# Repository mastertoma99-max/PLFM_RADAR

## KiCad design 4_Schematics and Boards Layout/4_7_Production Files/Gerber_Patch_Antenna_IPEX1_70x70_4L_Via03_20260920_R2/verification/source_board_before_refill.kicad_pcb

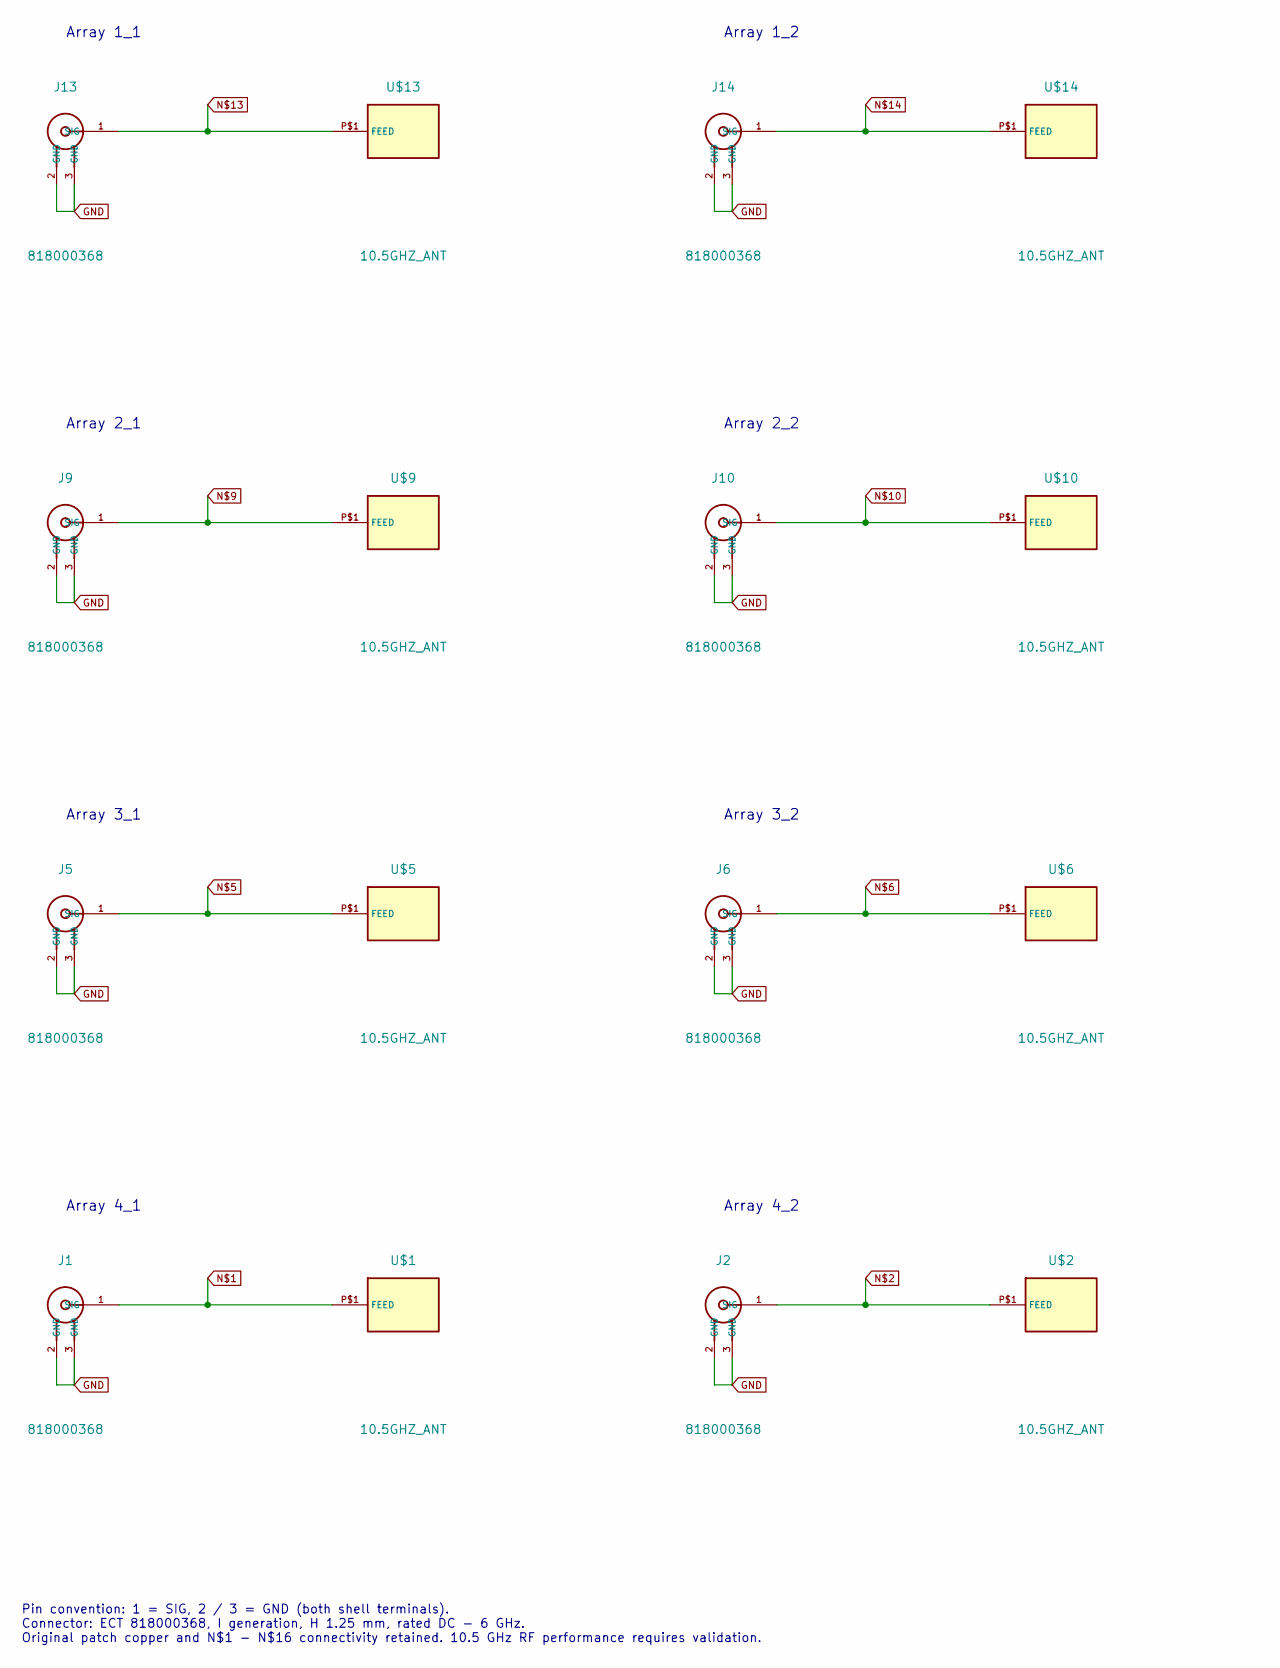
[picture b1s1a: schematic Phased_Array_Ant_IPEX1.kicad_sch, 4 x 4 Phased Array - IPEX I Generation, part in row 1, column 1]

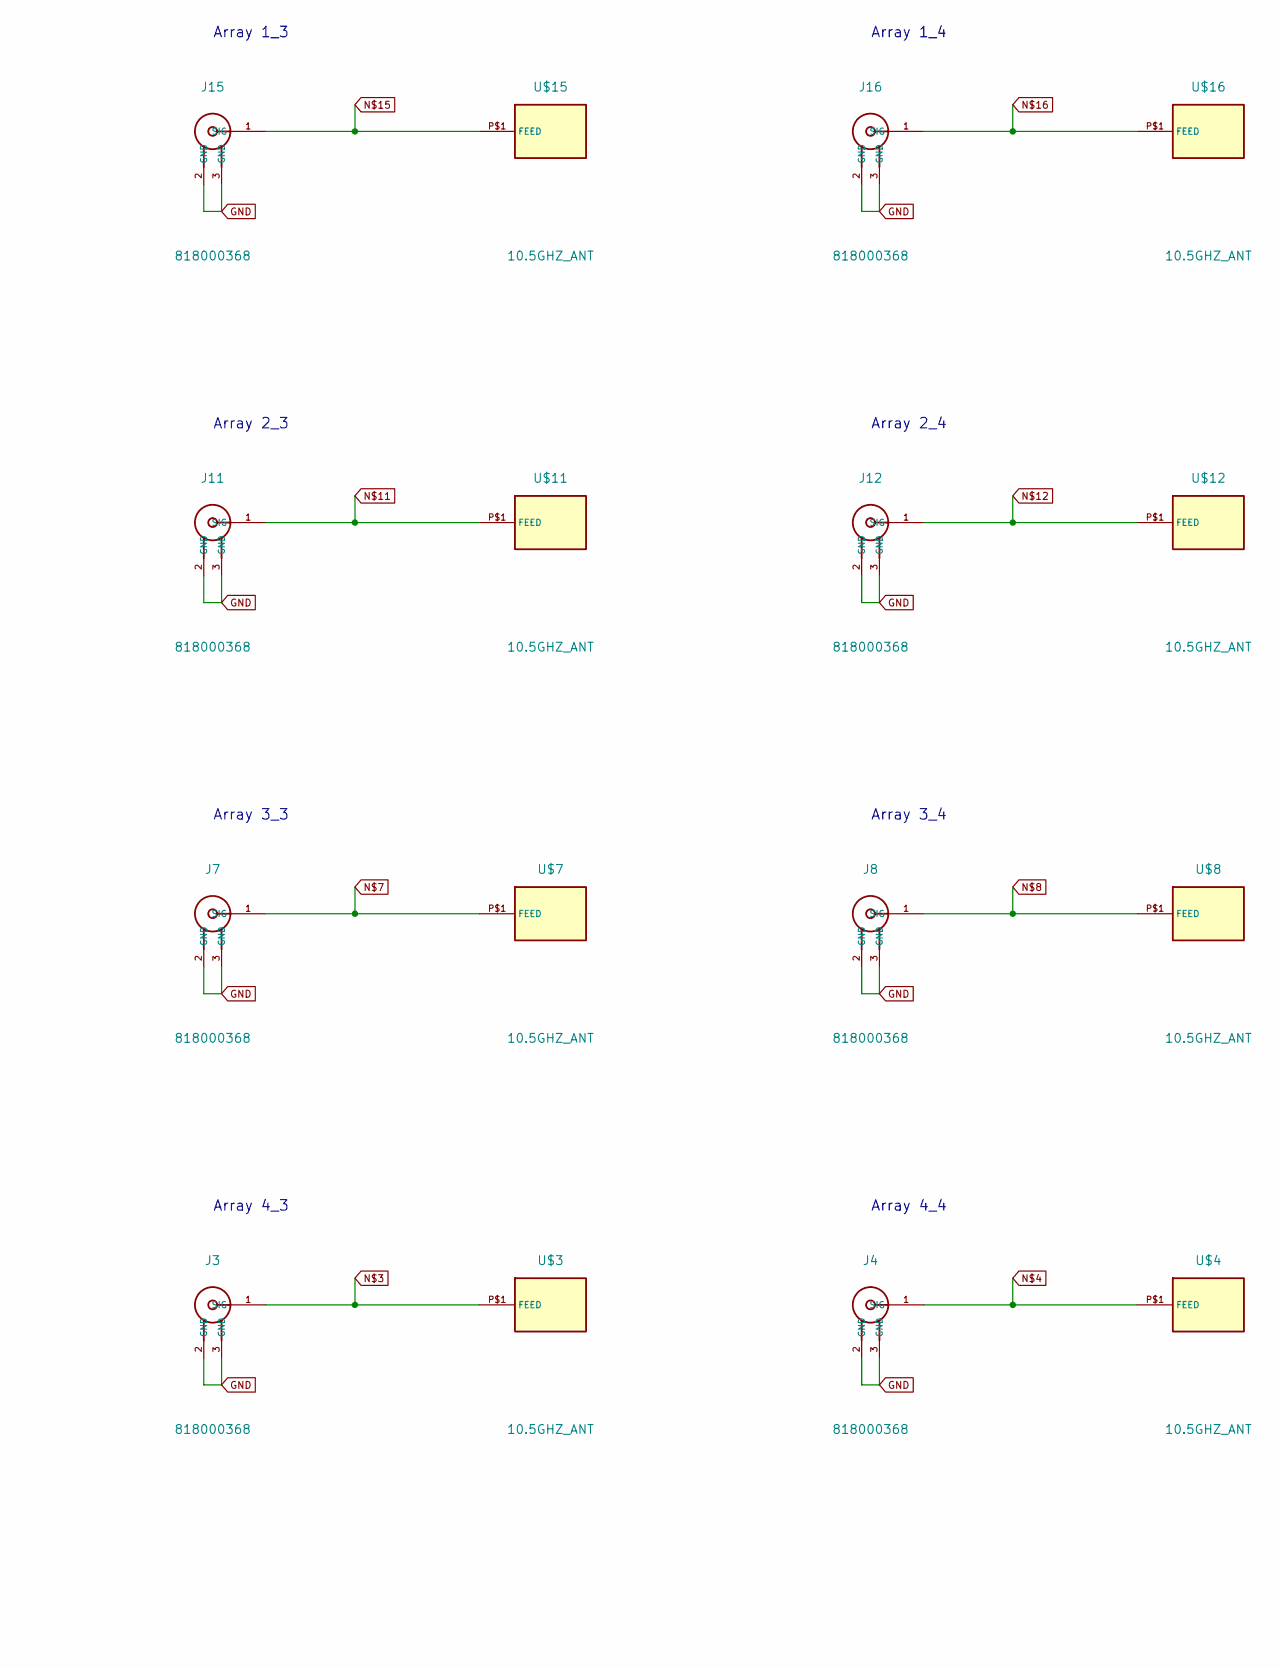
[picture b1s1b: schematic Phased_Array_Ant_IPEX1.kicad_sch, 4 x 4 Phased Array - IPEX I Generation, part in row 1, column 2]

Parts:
J1, J2, J3, J4, J5, J6, J7, J8, J9, J10, J11, J12, J13, J14, J15, J16: 818000368; ECT_818000368_IPEX1_1.25mm; MPN 818000368
U$1, U$2, U$3, U$4, U$5, U$6, U$7, U$8, U$9, U$10, U$11, U$12, U$13, U$14, U$15, U$16: 10.5GHZ_ANT; Patch_10p5GHz_9.538x7.636mm

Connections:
GND: J1.2 (GND), J1.3 (GND), J2.2 (GND), J2.3 (GND), J3.2 (GND), J3.3 (GND), J4.2 (GND), J4.3 (GND), J5.2 (GND), J5.3 (GND), J6.2 (GND), J6.3 (GND), J7.2 (GND), J7.3 (GND), J8.2 (GND), J8.3 (GND), J9.2 (GND), J9.3 (GND), J10.2 (GND), J10.3 (GND), J11.2 (GND), J11.3 (GND), J12.2 (GND), J12.3 (GND), J13.2 (GND), J13.3 (GND), J14.2 (GND), J14.3 (GND), J15.2 (GND), J15.3 (GND), J16.2 (GND), J16.3 (GND)
unnamed: J1.1 (SIG), U$1.P$1
unnamed: J2.1 (SIG), U$2.P$1
unnamed: J3.1 (SIG), U$3.P$1
unnamed: J4.1 (SIG), U$4.P$1
unnamed: J5.1 (SIG), U$5.P$1
unnamed: J6.1 (SIG), U$6.P$1
unnamed: J7.1 (SIG), U$7.P$1
unnamed: J8.1 (SIG), U$8.P$1
unnamed: J9.1 (SIG), U$9.P$1
unnamed: J10.1 (SIG), U$10.P$1
unnamed: J11.1 (SIG), U$11.P$1
unnamed: J12.1 (SIG), U$12.P$1
unnamed: J13.1 (SIG), U$13.P$1
unnamed: J14.1 (SIG), U$14.P$1
unnamed: J15.1 (SIG), U$15.P$1
unnamed: J16.1 (SIG), U$16.P$1

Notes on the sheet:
Array 3_4
Array 3_1
Array 1_4
Array 4_1
Array 4_4
Array 3_3
Array 1_1
Array 1_3
Array 2_3
Array 2_1
Array 4_3
Array 1_2
Array 2_2
Array 3_2
Array 2_4
Array 4_2
Pin convention: 1 = SIG, 2 / 3 = GND (both shell terminals). Connector: ECT 818000368, I generation, H 1.25 mm, rated DC - 6 GHz. Original patch copper and N$1 - N$16 connectivity retained. 10.5 GHz RF performance requires validation.

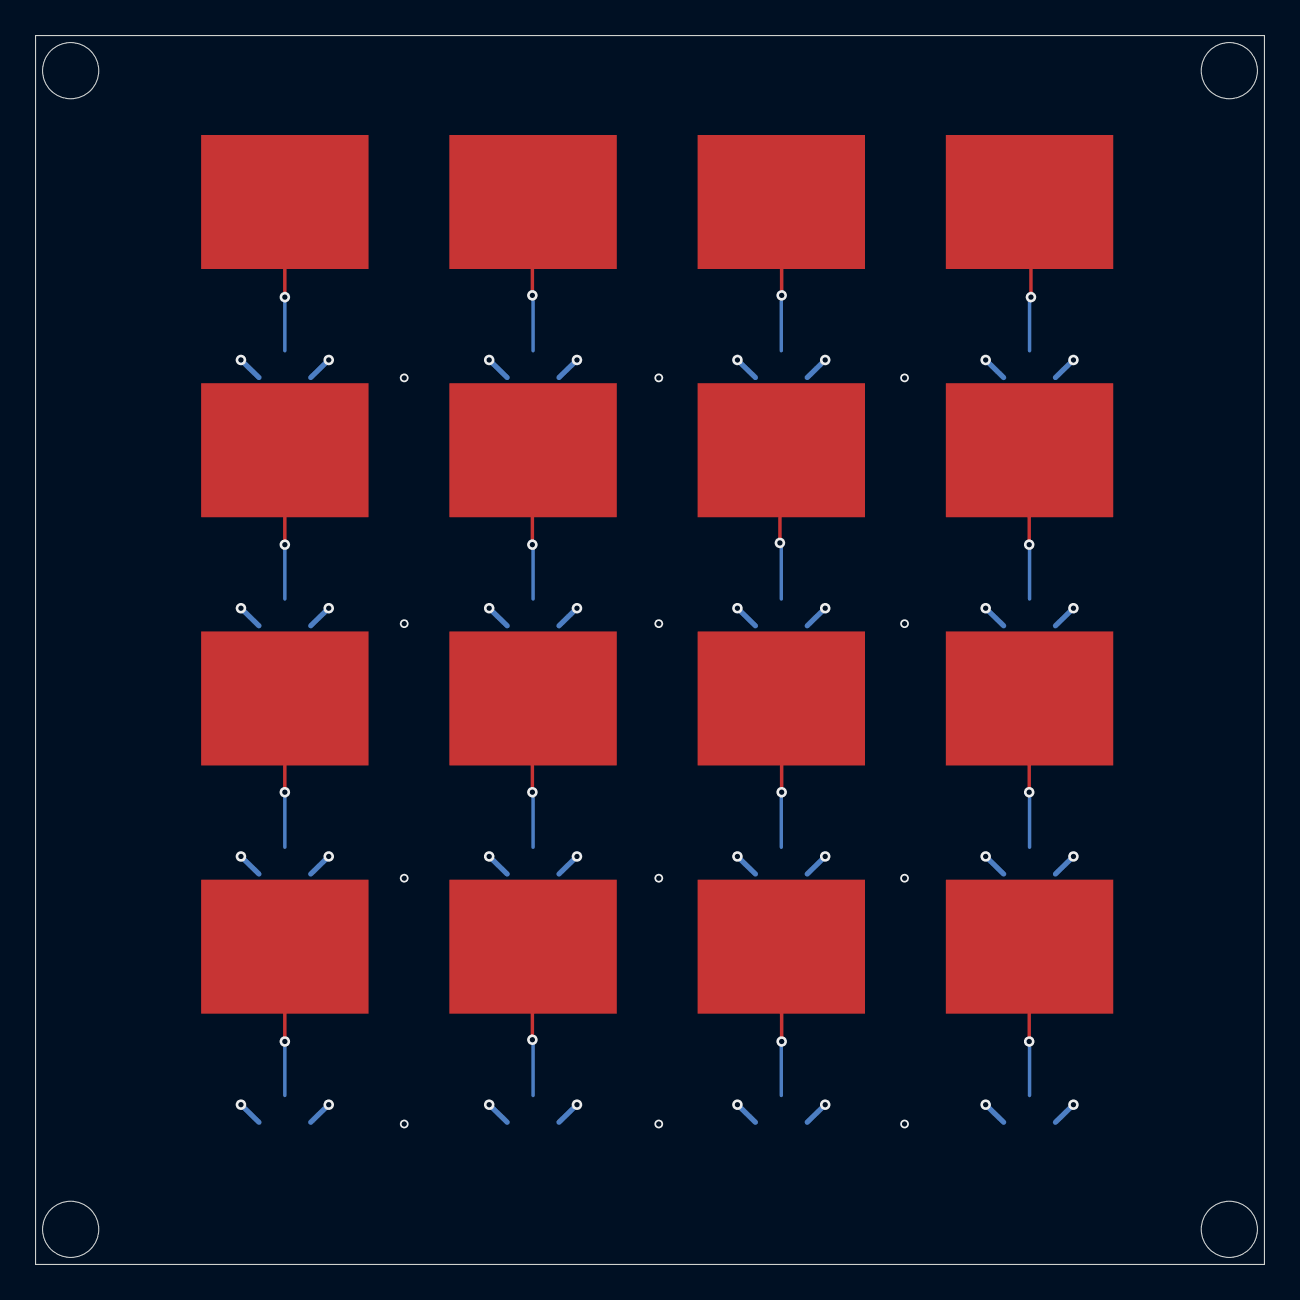
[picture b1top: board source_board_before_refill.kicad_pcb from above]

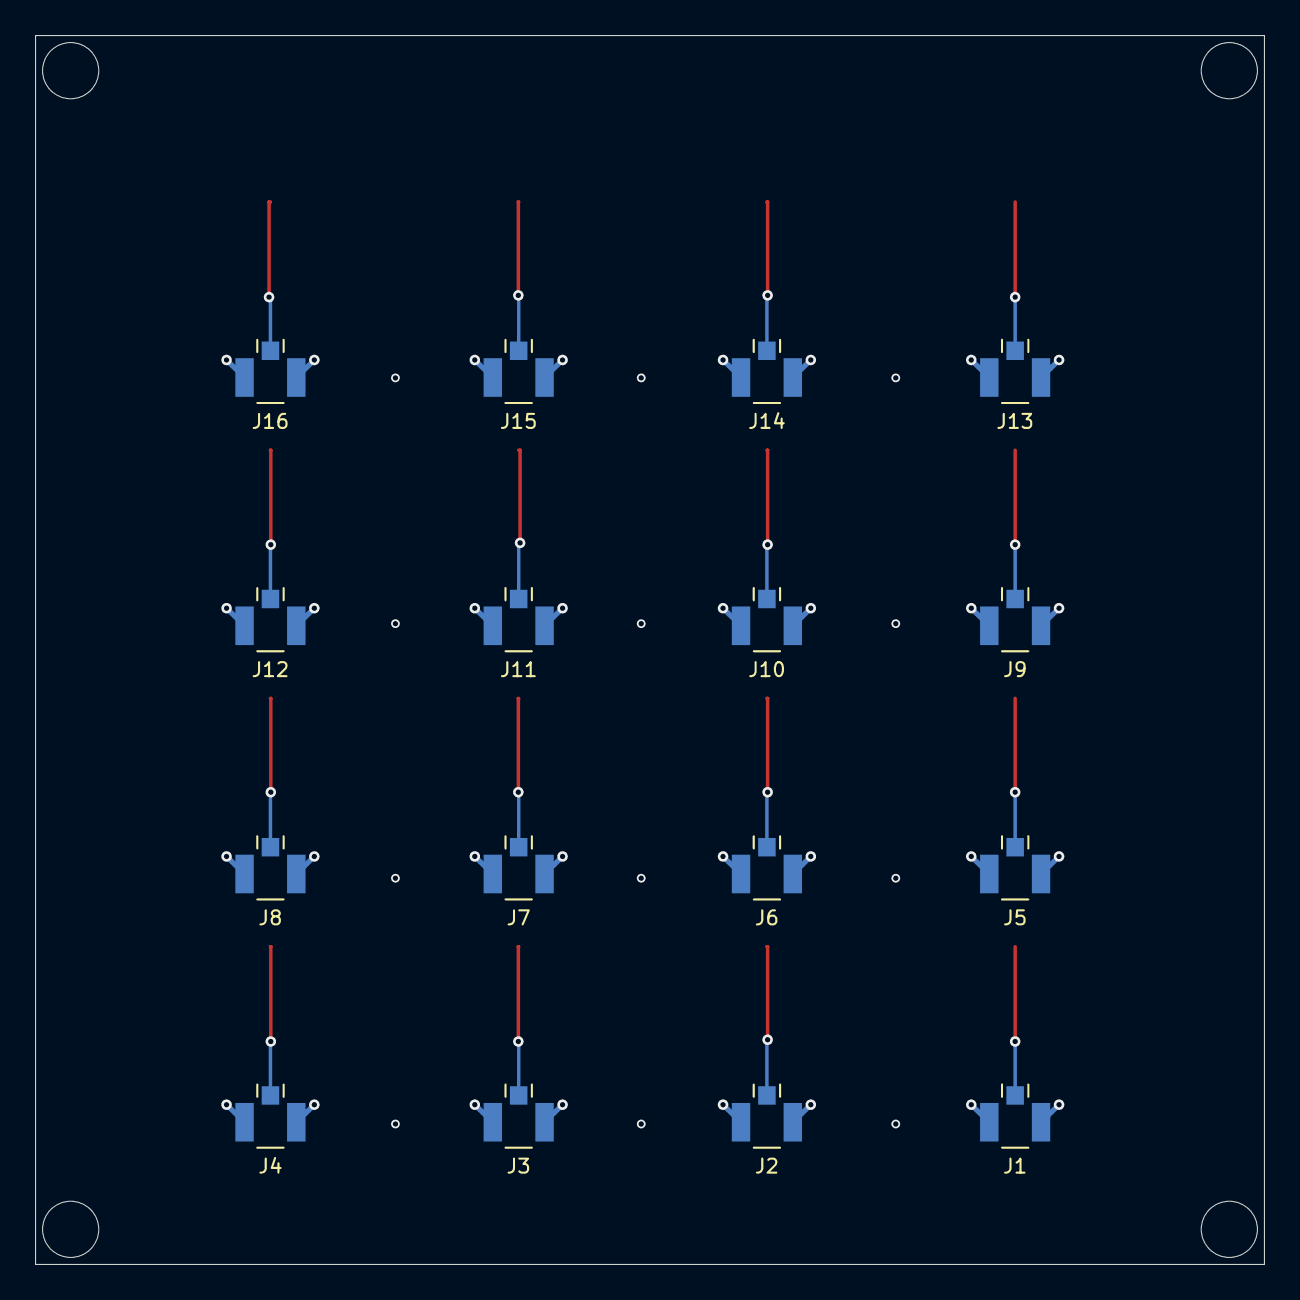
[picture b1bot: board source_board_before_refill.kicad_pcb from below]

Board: 4 copper layers, 70.0 x 70.0 mm, 36 parts (16 on the bottom side), 17 nets.

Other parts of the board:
UNK_HOLE_0, UNK_HOLE_1, UNK_HOLE_2, UNK_HOLE_3: MountingHole_NPTH_3.2mm
